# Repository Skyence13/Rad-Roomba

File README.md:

# Rad Roomba prototype design package

**System design revision 0.3 · 25 November 2026**  
An engineering baseline for a one-person-portable ROS 2 robot that surveys semitrailer and seacan floors at uranium facilities. The removable four-segment scintillation head is an independent hardware and firmware project. A dummy head lets the mobile platform proceed in parallel.

## Start here

1. Read **docs/Rad_Roomba_Design.pdf** for the full design, operating concept, decisions and gated development plan. Use **docs/Rad_Roomba_Design.docx** to revise it. The source register is in **docs/Sources.csv** and citations are clickable in both documents.
2. View **cad/renders/Rad_Roomba_Rev_D_Assembly.png** for the assembled robot and **cad/renders/Rad_Roomba_Rev_D_Detector_Head.png** for the detector detail. Open **cad/Mechanical_layout_D.pdf** for the three proposed mechanical views. Open **cad/Rad_Roomba_D.step** for the entire assembly or **cad/Detector_Head_D.step** for the removable head. Native source, dimensions, rebuild and geometry checks are in **cad/**.
3. Use **planning/requirements.csv** and **planning/verification.csv** together. Filter by owner and gate, attach evidence to a test, and update the linked requirement. **planning/risks.csv** and **planning/decisions.csv** track unresolved hazards and choices. Gate assignments run from G0 site inputs to G4 controlled pilot.
4. Use **planning/Detector_Head_RFQ.md** to request one full-size optical pair and comparable pricing for four. Use **planning/detector_bench_runs.csv** to capture test results; the RFQ explains its fields. Use **planning/Rad_Roomba_Current_BOM.xlsx** or **planning/prototype_bom.csv** for the current parts. Use **planning/Survey_Field_Checklist.md** for commissioning, shared-space scanning and guided follow-up, the separate secured unattended option, and charge service.
5. Read **interface/head_icd.md** before integrating the head. The samples under **examples/** show the wire and frame formats, geometry and site settings. **software/** contains a separate end-to-end mapping example for already-decoded data and the resulting map. Its input CSV is a simulation fixture. Read **software/Operator_Interface.md** for the operator workflow and open **software/guide_demo.html** in a browser to try the offline review queue.

## Project files

| Path | Use |
|---|---|
| docs/ | Full design in Word and PDF. Primary sources are indexed by ID in Sources.csv. |
| cad/ | Rev D editable assembly source, neutral STEP models, three-sheet PDF, dimensions and geometry checks. Coordinate units in the models are millimetres. |
| interface/ | Proposed modular head mechanical, power, independent bumper and isolated RS-485 contract. Includes the head descriptor, discovery, acquisition schema, CRC codec, host validation and tests. |
| examples/ | Normal and degraded frame, decoded transactions, a CRC-framed response, a head descriptor and bench registry, a concept geometry manifest and disabled site-profile examples. Units are explicit in files and in the ICD. |
| software/ | Python offline map demonstration, raw synthetic counts, poses, calculated cell estimates, valid exposure and a portable SVG. Also includes the operator web specification and an offline guided-tour demo with personnel present. |
| planning/ | Procurement crosswalk, OEM RFQ, operator checklist, detector run sheet, requirements, verification, risks and decisions. CSV files open in a spreadsheet editor. |
| reference/ | Original hardware workbook, user-supplied concept sketches, first concept and the preceding Revision B models. The current models are in cad/. Superseded Rev C models are in cad/previous_C/. |
| SHA256SUMS.txt | SHA-256 digest of each distributed file, excluding the checksum list itself. |

## Reproduce the included checks

From the unpacked **Rad_Roomba_Design_Package** directory:

```sh
python3 software/map_demo.py --self-test
python3 software/map_demo.py --out local_demo
```

The map example uses the Python standard library. The head interface tests additionally require the Python package **jsonschema** supporting Draft 2020-12. In an environment with it installed, run:

```sh
python3 interface/test_interface.py
```

For CAD, follow **cad/README.md**. The neutral STEP models and mechanical PDF are usable without rebuilding the CadQuery sources. On systems with GNU coreutils, check extracted file integrity from this directory with `sha256sum -c SHA256SUMS.txt`.

## Changes in revision 0.3

**Technicians in the trailer.** The intended shared-space mode permits technicians to stay in the trailer through a scan and while the robot moves between flagged areas. A person can stand alongside or behind the robot where there is sufficient clearance for the requested move. Determine the protected region from the body and projecting head throughout that move, detection latency, measured braking on the actual floor and a person's possible approach. A blocked route holds. For a hands-on check, inhibit traction, perform the check and step clear of the local motion envelope before deliberately restoring permission. The design also retains a separate secured, unattended option. Shared-space operation requires demonstration of personnel protection on the assembled robot. See the operator workflow and verification register.

**Head identity and acquisition.** Each attachment establishes the head type, serial, boot and descriptor once during discovery and binding. Subsequent count traffic carries interval measurements, timing, sequence and health. The host saves an attachment record and links every stored count to that record. Disconnection, reset, or loss of confidence in continuity requires re-establishing the binding. Recoverable packet loss on an intact connection uses the existing binding. The example transactions and tests in interface/ and examples/ show the distinction.

**CAD views.** The two standalone studio views in cad/renders/ come from the existing mechanical Rev D assembly and head. They share the same nominal dimensions as the engineering drawings.

## Changes introduced in revision 0.2

| Design review topic | Current location | Requirement |
|---|---|---|
| Shared web interface, gloved local controls, deliberate command authority | Design §2 and §7, software/Operator_Interface.md | RQ-041, RQ-042 |
| Qualified unattended scans, protective access controls and guided hotspot visits | Design §2, §4 and §7, offline guide_demo.html, operator field checklist | RQ-010, RQ-039, RQ-040, RQ-043 |
| Swappable packs, charge inlet, limited settings/data service | Design §4 and §8, current BOM workbook and rows R01–R06 | RQ-044, RQ-045 |
| Head-mounted MCU, identity, geometry and laboratory patch harness | Design §5–6, interface/head_icd.md, examples/head_descriptor.json | RQ-046, RQ-049 |
| 10 mm entrance gap, 3 or 5 mm rail projection and cantilever dynamics | Design §4–5, cad/Mechanical_layout_D.pdf, planning/detector_bench_runs.csv | RQ-047, RQ-048 |
| Pose at acquisition and saved locations for hand surveys | Design §1, §2 and §7, operator field checklist | RQ-050 |

The offline guide uses synthetic flags and no hardware connection. The proposed production web service, motion system and protective interlocks require implementation and field qualification.

## Baseline and use

The original workbook provides the 12.8 V / 8 Ah trial pack, warm-start power worksheet and prototype parts. The current procurement workbook adds the detector MCU, connector and bench kit, removable battery and charging hardware. Its sizing sheet models average consumption separately from peak supply allocation. The Rev B survey bar is a narrow placeholder. Rev C lengthened the head for four 80 × 100 mm apertures and separate upper references. Rev D retains that footprint, sets the entrance 10 mm above a level floor, and models a 7 mm clearance under the compliant contact rails. A 12 kg all-up packaging allowance and a one-hour energy scenario are trial assumptions. Weigh and qualify the real system for the actual site workflow.

The ore profile carries the stated 0.30 Bq/cm² investigation level and 0.40 Bq/cm² comparison criterion. A moving detection limit below 0.20 Bq/cm² is a proposed qualification target for a yet-to-be-specified minimum patch and field. The yellowcake profile awaits the radiation protection team's procedure and calibration. Raw counts and source, timing, location, coverage and sensitivity evidence remain essential to interpreting a reported Bq/cm² value.

All planning-register tests begin open. The software fixtures and CAD checks can be reproduced now. The build still requires component qualification, physical stopping and cold tests, radiometric calibration, independent field comparison and site authorization. Follow the evidence gates before treating the robot as an operational survey instrument.

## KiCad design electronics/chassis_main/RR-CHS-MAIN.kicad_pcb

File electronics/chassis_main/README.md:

# RR-CHS-MAIN rev A — chassis main board (stage 2, KiCad 9)

| | |
|---|---|
| Netlist source | `design/circuit.py` (stage 1, reviewed baseline, **not edited**) + `overrides.py` (stage-2 deviations S2-xx, stage-3 review fixes S3-xx and stage-4 follow-up fixes S4-xx, applied and checked on every build) |
| Board definition | `board.py` (libraries, import, notes) · `placement.py` (floor plan, net classes, planes, keep-outs, routing settings) · `placement_auto.py` (frozen auto-arranged passives, generated by `tools/freeze_auto.py`) |
| Board | 160 × 100 mm, **6 layers** (F sig / In1 GND / In2 sig / In3 sig / In4 power splits / B sig), 1.6 mm; 881 parts (768 − 1 removed + 3 stage-2 + 111 stage-3/4/5), 484 nets, 19 A3 schematic sheets |
| Status | see `STATUS.md`; routing result in section "Routing" below |

## Commands

```
python3 electronics/chassis_main/design/circuit.py          # stage-1 self-check (baseline)
python3 electronics/chassis_main/overrides.py               # stage-2 change log + self-check on the overridden netlist
python3 tools/eda/rrkicad.py sch   electronics/chassis_main/board.py              # schematic, netlist cross-check, ERC, PDF (~10 s)
python3 tools/eda/rrkicad.py build electronics/chassis_main/board.py --no-route   # + placed PCB, fan-out, escape, DRC, outputs (~2 min)
RR_FREEROUTING_JAVA_OPTS=-Xmx6g python3 tools/eda/rrkicad.py build electronics/chassis_main/board.py   # + autorouter (route/ SES cached)
tools/docker/kicad.sh python3 electronics/chassis_main/tools/fitcheck.py         # courtyard area per side, zone checks -> reports/fitcheck.json
python3 electronics/chassis_main/tools/cable_lengths.py                          # board-side list of the harness generator's lengths -> reports/cable_lengths.json
python3 electronics/chassis_main/tools/near_report.py 10                         # passives farther than 10 mm from their anchor pin
python3 electronics/chassis_main/tools/freeze_auto.py                            # freeze auto-arranged parts after a build
```
Delete `placement_auto.py` to let the auto-arranger re-place the passives (then freeze again).

## Frame mapping

`mechanical/common/board_envelopes.yaml` RR-CHS-MAIN (u, v) → tool board frame **(X, Y) = (u, v)**, no rotation, no offset:
origin = rear-left corner seen from above, X = u towards the robot's right (base_link −y), Y = v forward (base_link +x), top side up.
base_link = (−67 + Y, 80 − X, 83 + z) mm (board top at z = 84.6). Holes H1..H6 at the envelope (u, v); IMU U42 centred at (80, 67);
THERMAL_TO_BRIDGE pad u 50–110, v 30–70; front corners u < 14 / u > 146, v > 88. The pick-and-place file, `out/pinmap.json`, the STEP
models and the drill origin all use this frame.

## What is tool-checked (and what is not)

| Check | Result (last `--no-route` build, stage 5, 2026-11-28) |
|---|---|
| ERC | 0 errors, 0 warnings |
| Netlist cross-check: generated schematic → KiCad netlist vs definition, pin by pin | OK, 881 components (definition = circuit.py + overrides S2-S5) |
| DRC (placement, incl. the stage-3/4 custom chain rules: 7 rules in `RR-CHS-MAIN.kicad_dru`) | **0 errors**; 230 warnings (silk overlap 86, silk over copper 73, silk edge 9, dangling escape vias 61, copper sliver 1); schematic parity 0; courtyard overlaps 0; **1252 unconnected = board not routed** |
| Envelope | `tools/fitcheck.py`: no part outside the outline, no bottom part in the gap-pad area |
| Utilisation (courtyard area / 16 000 mm²) | top 59.5 %, bottom 21.9 % |

Not tool-checked: 1.0 mm between adjacent chain nodes (see "Clearances"), current capacity of the routed copper,
impedance of the USB / RS-485 pairs, thermal performance, real component heights (3D models are bounding-box envelopes).

## Placement

* Explicit (`placement.PLACE`, 148 parts): every connector (edge headers aligned to the edge from their real courtyards), relays,
  inductors, electrolytics, FETs, shunts, TVS, every IC, and the parts the guidance wants at the pins (bridge charge-pump / VM
  capacitors, crystal network, U10 boot/VCC). Floor plan as `layout_guidance.md` §2: power entry / charger / latch at the right rear,
  bridges, VMOT eFuse, 5 V buck and clamp on the gap pad, MCU + logic left, head branch front-left, RS-485 front-right.
* Passives (623): auto-arranged with `near=` the IC/connector pin they share a net with (`placement.auto_near`), on the side of that
  part (bottom for connector and through-hole anchors), then frozen. Quality (`reports/near_report.json`, test points excluded): of
  504 anchored passives 144 are ≤ 5 mm, 135 5–10 mm, 156 10–20 mm and **69 more than 20 mm** from their anchor pin (greedy auto-arranger
  on a dense board). Those are the first thing to improve by hand.
* Connector moves (IB-12 / IB-33): rear-right cluster = J_ESTOP, J_HANDS, J_COVER, **J_BUMP_R** (CLIK-Mate row) and J_NTC, **J_PAUSE**,
  **J_TOF3**, **J_TOF10**, **J_TOF6**, J_PAUX (GH rows); rear-left = J_MODE, J_BTN, J_BUMP_L, J_TOF9/8/2, J_PANEL, J_TOF5, USB, debug.
  Estimated ToF cables all ≤ 300 mm (`STAGE2_CHANGE_REQUESTS.md`).
* Outputs for the mechanical fit check: `reports/placement/RR-CHS-MAIN-unrouted.step`, `placement-top.png`, `placement-bottom.png`,
  `placement-assembly-top.pdf`, `placement-assembly-bottom.pdf`, `placement-copper-unrouted.pdf`, `RR-CHS-MAIN-pos.csv`.

## Copper

* In1.Cu: solid GND. In4.Cu splits (non-overlapping): 3V3 (logic, u 0.5–50, v 27–62), VMOT (u 58–102, v 37–62), VSYS (charger,
  u 104–159.5, v 42–60), VBAT_SW (rear band and right side, and the front-left head-branch area). rrkicad's plane fan-out ties SMD
  pads of those nets to their plane.
* Net classes: HC_PACK 1.0 mm, HC_VMOT / HC_BRANCH 0.8 mm, PWR_1A5 0.4 mm, SAFETY_CHAIN 0.4 mm / 0.2 mm clearance, signals 0.2 mm.
  These are the autorouter widths; the guidance widths for 20 A / 6.5 A / 5 A (12.3 / 2.6 / 1.8 mm) need pours or hand-drawn
  copper that is **not yet done** (open item).
* Keep-outs: 7 mm around every mounting hole (vias, parts), no vias under the IMU, no bottom parts on the gap pad.

## Clearances (stage 3, review M6: enforced by DRC)

* SAFETY_CHAIN net class (`placement.CHAIN_NETS`): 0.5 mm clearance to everything (the tool's plane fan-out now uses pairwise class
  clearance, `tools/eda/STATUS.md` defect 3).
* Custom DRC rules, written by `board.py` to `RR-CHS-MAIN.kicad_dru` from `placement.chain_rules()`; KiCad's DRC (kicad-cli, the tool's
  DRC step) loads the file from the project directory: **1.0 mm** from every high-side chain node (`CHAIN_HIGH`: CH_N0…CH_N9, CHAIN_END,
  K1_RUN, RUN_HD, RUN_12V, K1 coil / seal / set nodes, SET_CAP) to every supply net (`SUPPLY_NETS`: pack, VBAT_SW, VSYS, VMOT, V12_AUX,
  bridge outputs, branch outputs); **2.0 mm** loop-sense nets to heater nets (J_HEAD1 pins 4/5 are adjacent by contract and exempt as a
  pad pair); **10 mm** pad-to-pad between a chain test point and any other chain or supply test point (one bench clip cannot bypass an
  element; TP8/9/38/39/40/50/60/61/62 placed explicitly).
* In4 VBAT_SW / VMOT / VSYS splits: 1.0 mm zone clearance.
* Not covered by a rule: 1.0 mm between *adjacent* chain nodes (only the 0.5 mm class clearance), and the coil returns / clamp cathodes
  against GND (a GND short there is the low-side analogue of a bypass and cannot be kept away from the GND plane).

## Library resolution (the 15 parts without a footprint and the rejected symbol hints)

| Parts | Resolution | Geometry source |
|---|---|---|
| J_MODE, J_ESTOP, J_HANDS, J_COVER, J_DOCK, J_BUMP_L, J_BUMP_R, J_BTN | stock `Connector_Molex:Molex_CLIK-Mate_502443-xx70_1xNN-1MP_P2.00mm_Vertical` (MP solder tabs left without net) | KiCad library |
| U13, U16–U19 (TPS259470, RPW VQFN-HR-10 2 × 2) | `rr_local:TI_RPW0010A_VQFN-HR-10_2x2mm_PLACEHOLDER` | **from memory, PLACEHOLDER — redraw from the TI drawing** |
| U10 (LM61460, RJR VQFN-HR-14 4 × 3.5) | `rr_local:TI_RJR0014A_VQFN-HR-14_4x3.5mm_PLACEHOLDER` | **from memory, PLACEHOLDER** |
| W1 (DNP wire pads) | `rr_local:WirePads_2x2.5mm_P5.0mm` | stage-1 description |
| also: U8 TPS25982 (hint not a library name) | `rr_local:TI_TPS25982_VQFN-24_4x4mm_SplitPad_PLACEHOLDER` | generic QFN-24 perimeter, split pad **from memory** |
| L3, L4 (WE-LQS 5040) | `rr_local:L_Wuerth_WE-LQS-5040` | pads estimated from the 5 × 5 body, **verify** |
| L2 (XAL6060) | stock `L_Coilcraft_XAL6030-XXX` (same 6.36 × 6.56 base) | KiCad library, family assumption **verify** |
| Q4, Q5, Q40 (CSD18543Q3A) | `rr_local:VSON-8_3.3x3.3mm_P0.65mm_NexFET_G0.2` | stock NexFET land with pads 1–4 0.45 mm tall (stock 0.5 mm leaves 0.14 mm < fab 0.15 mm) |
| U42 (BMI088) | `rr_local:Bosch_LGA-16_4.5x3mm_P0.5mm_ClockwisePinNumbering` + local symbol `BMI088_SPI` (SDO tri-state) | pads copied from the stock Bosch footprint without its internal keep-out (the fan-out ignored it) |
| U5, U6 (DRV8874) | stock HTSSOP-16 EP variant without thermal vias (stage-1 hint has 0.2 mm drills) | KiCad library |
| U15, L60, SW1/2, TPs | stock `Texas_RGV0016A_VQFN-16…`, `L_CommonModeChoke_Coilank_ACM2012` (pin pairing **verify**), `SW_Tactile_SPST_NO_Straight_CK_PTS636Sx25SMTRLFS`, `TestPoint_Keystone_5019_Miniature` (hint misspelt) | KiCad library |
| Symbols | SOT-23 FETs → `Transistor_FET:BSS138/BSS84`, power FETs → `CSD18540Q5B/CSD18543Q3A`, U45 → `TCA9534`, K2/K3 → `Relay:G2RL-2` (renumbered S2-06b), J_HTR/J_LIDAR → `Conn_01x02`, shunts → `Device:R` | 12 generated box symbols remain (all-passive pins): LM74502, LTC4162-F, LM61460, LMR51610, TPS259470, INA3221, TPS2553, TPS3430, TPS25982, DRV8874, SM712, AOD4185 |

## Deviations from stage 1

`STAGE2_CHANGE_REQUESTS.md` (full list with reasons). Netlist/BOM: S2-01 J_PAUSE split from J_BTN (+R_PAUSE, D_PAUSE, D29 channels),
S2-02 J_HEAD1 → Mini-Fit Jr 2x5 (AWG 18), S2-04 R46 845 Ω (HEAD_HTR 3.96 A), S2-05 U42 pin 2 GND. Renumbering S2-06, library S2-07.
Decisions without netlist change: J_CM5 stays Micro-Fit with AWG 20 harness (IB-32 numbers), IB-28 contract proposals, IB-37 accept
offset. Placement: 6 layers, connector moves (IB-12/33).

**Stage 3 (review fixes, `docs/reviews/REVIEW_traction_inhibit.md`), S3-xx:** on-board edge-triggered two-contact REARM set stage
(U_SET, the K1 coil node no longer leaves the board), second diverse hold element U_HOLD in series with K1 pole B, D_RUN and the
low-side relay-return element U_LS (a RUN_12V short no longer energises the brake relays), K1 NC and K1_RUN readbacks, D_RSET (no
C_SET back-feed) and an active C_SET discharge, a second diverse head-loop channel (U46 + U21B in series), 47 kΩ isolation of every
expander pin on a chain-control node, U9 on its own tap, stiffer PB12/PD2 taps, IOX_D (U47, TCA9534 0x22), K2/K3 clamp Zeners 20 V,
chain clearance rules and test-point spacing. **Stage 4 (follow-up review `docs/reviews/REVIEW_traction_inhibit_followup.md`), S4-xx:** SET_READY comparator (U33B) and third stack FET Q_SETC (an early REARM press no longer empties the reservoir; readiness readable), R_SET 15 k, set qualification C_SF 2.2 µF (≥ 3.2 ms press), REARM set contact on IOX_A GPB6 at 1 kHz, CH_N6A tap and loop self-test FETs on IOX_D, D_RUN silicon + RUN_HD bleed, channel-B threshold 1.89 kΩ, own discharge-gate divider, D29 replaced by a 15 V D_AUX, net class CHAIN_CTRL and extended DRC rules (logic supplies, LED/gate nodes). Firmware list G1-G12 in `STAGE2_CHANGE_REQUESTS.md` section "Stage 4". **Stage 5 (`docs/reviews/REVIEW_traction_inhibit_stage4.md`), S5-xx:** top-side service pads SVC1-SVC10 (TP63-TP72, centre (133.0, 79.5)) with 220 k protection resistors R_SV2-R_SV10 for the latent-fault service tests (no test needs the board out), GPB6 readback 10 k/47 k + clamp, analog loop copy from LOOP_SNS, RT1 moved next to K1; firmware list H1-H7, body/harness notes §5.3. Full list, firmware change list (F1-F18) and harness/mechanical consequences:
`STAGE2_CHANGE_REQUESTS.md` section "Stage 3". Analysis: `electronics/analysis/chassis_safety_chain.md`.

## UNVERIFIED / open items

* PLACEHOLDER land patterns: U8, U10, U13, U16–U19 (redraw from TI drawings before fabrication); L3/L4 pads estimated; L2 family land.
* L60 common-mode choke winding pairing (1-2/4-3 vs 1-4/2-3) — a wrong pairing shorts RS-485 A to B through a winding.
* All stage-1 `verify=True` parts (132, BOM notes) plus the parts marked by stage 2 (`reports/summary.json` → `bom.verify`), notably
  LTC4162-F pin table, G2RL-2 / G6S-2 contact numbering, BMI088 pin numbers, TCA953x / MCP23S17 / FT230X pin numbers, Mini-Fit Jr MPNs.
* High-current copper (pours/pre-routes for HC_PACK 20 A, VMOT 6.5 A, heaters, V5_CM5 5 A), Kelvin routing for the shunts, USB/RS-485
  pair pre-routes, safety-chain grouping on L1: not done in this pass.
* 69 passives > 20 mm from their anchor pin (`reports/near_report.json`).
* Look sensors resolved (DEC-043): J_TOF4 = LOOK_FL, J_TOF5 = LOOK_RL, J_TOF6 = LOOK_RR, J_TOF7 = LOOK_FR (descriptions S3-N1).
* Stage-3 parts were placed by the auto-arranger and then frozen (`placement_auto.py`); U_SET/U_HOLD/U_LS/U21B/U46/U47 and their passives are not where a designer would put them (e.g. U21B and U46 apart, U_SET/U_HOLD 25 mm from K1): hand placement is the next step, before routing.
* Stage-3 UNVERIFIED: TLV3201 DBV pinout, TCA9534 pin table, B160 rating, TLP241A data, G6S-2 must-operate/release, TCA953x/STM32 input thresholds and pull-down values (STAGE2_CHANGE_REQUESTS.md 3.4). TPS3430 is now verified [D].
* Silkscreen: connector function legends, safety yellow box and "NOT A SAFETY-RATED CIRCUIT" text not yet added (references only).

## Routing (attempt of 2026-11-27, tool as it stood then)

> **Superseded by stage 3.** The stage-3 netlist (S3-xx) invalidates this routing: `RR-CHS-MAIN.kicad_pcb` is now the `--no-route` build of the stage-3 definition (**not routed**); the SES cached in `route/` belongs to the stage-2 netlist and must not be re-imported. The record below is kept for the routing engineer.

Run: `RR_FREEROUTING_JAVA_OPTS=-Xmx6g python3 tools/eda/rrkicad.py build electronics/chassis_main/board.py` with
`placement.routing()`: one Freerouting run, 780 s cap, no continue runs, rrkicad fine-pitch escape (default on for 6 layers;
`tools/eda/STATUS.md` reports it implemented and passing on STRESS-150, the README not yet updated) and the finisher.

| | |
|---|---|
| Plane fan-out / escape | 537 fan-out vias on GND, 3V3, VBAT_SW, VMOT, VSYS (154 pads left to the router); escape 82 vias + 2 direct pre-routes on U20M, U3, U42, U61, U8 (64 pads skipped, `reports/routing/summary-routed.json` → `routing.escape`) |
| Freerouting | 1169 unrouted items at start; **pass 1 took 769 s** (host load average 11-19 on 4 cores, other agents' builds), stopped by the 780 s cap after that pass with **802 unrouted** (score 403) |
| Result in KiCad (`RR-CHS-MAIN.kicad_pcb`) | 2486 tracks, 970 vias; **802 open connections** (KiCad ratsnest; DRC lists the first 499: `reports/open_connections.txt` with nets and coordinates); DRC **1 error** (shorting_items: an RS_RO via through the NT1 net-tie copper polygon, see tool defects), 145 warnings (silk 119, 25 dangling escape vias, 1 dangling track); schematic parity 0; ERC 0/0 |
| Status | **FAIL** — partially routed. Planes, fan-out, escape pre-routes intact; the SES is cached in `route/` |
| Time | build 00:48 → Freerouting end 01:03 (820 s routing) + post stage 38 s |
| Open connections by net (first 499 listed) | V5_AUX 27, 3V3 14, VREF_3V0 13, V5_BUCK 10, VBAT_RAW 8, VBAT_SW 8, CHG_VIN 8, COIL_RTN 8, PSW_SRC 7, RUN_12V 7, HW_LATCH_RB 7, VSYS 6, … (power nets dominate: their pads were left to the router where no fan-out via fit) |

How the post stage was run: the build's own `_post` crashed in the tool's new unused-escape clean-up
(`pcb.py _remove_unused_escapes`: `TypeError: 'SwigPyObject' object is not iterable`; pcb.py was being edited during the run) and
the host then started the finisher on an un-imported board (1165 "open"), which was stopped. The SES was imported with
`tools/docker/kicad.sh python3 tools/eda/rrkicad.py _post electronics/chassis_main/board.py` after moving
`route/escape_vias.json` aside (that file only drives the clean-up), so unused escape vias remain (25 via_dangling warnings).
A plain `build` re-uses the cached SES but will hit the same crash until the tool is fixed.

Judgement — what it takes to finish: the router is CPU-starved and far from done after one pass (31 % of the items routed in
13 min); STRESS-150 needed ~20-40 passes. Realistic routes to completion, in order of effect: (1) hand-drawn copper for the power
nets that dominate the open list (pours/pre-routes for VBAT_RAW/PSW_SRC/VBAT_SW at the power entry, VMOT, VSYS, V5_BUCK/V5_CM5,
heater branches) and extend the In4 splits / add In3 pours for V5_AUX and VREF_3V0; (2) fix the ~70 passives placed > 20 mm from
their pins and the dense rear-left corner; (3) then several continue runs of 20-30 min each on an otherwise idle machine plus the
finisher once the tool's import is fixed; (4) whatever remains (expect tens of connections) by hand in KiCad. The safety-chain group
routing and the critical-net pre-routes of guidance §6 are not done and should precede (3).

Next fixes in the definition (not applied, to keep the routed files consistent with `board.py`): copper + via keep-out over NT1
(Freerouting does not see net-tie polygons), the 6 pin-to-pin "violations" Freerouting reports on U1 (SOT-23-8 0.15 mm gaps + 25 um
DSN margin) are harmless.

## Tool defects found (tools/eda not edited; worked around in the board definition)
1. Plane fan-out places vias with the via net's class clearance, not the neighbour's → SAFETY_CHAIN DRC clearance lowered to 0.2 mm.
2. Plane fan-out ignores footprint-internal rule areas (Bosch LGA keep-out) and net-tie copper polygons → local IMU footprint without
   rule area + board via keep-out; NT1 moved and `zone_connect="none"`; Freerouting likewise routed a via through NT1's polygon.
3. A footprint-only rule area on B.Cu (no tracks/vias/copper ban) is exported to the DSN as a full B.Cu keep-out → removed once the
   placement was frozen.
4. KiCad's DRC report lists at most 499 unconnected items, so `summary.json` → `unconnected` saturates at 499 (true count 802 here
   after routing); the summary should use the connectivity count.
5. Post stage crash in `_remove_unused_escapes` (above) and the host then running the finisher on an un-routed board.
6. Auto-arrange is weak on dense two-sided boards (69 passives > 20 mm from their anchor pin); with escape keep-aways it can fail
   ("no room") when passives are asked to stay on the IC's side.

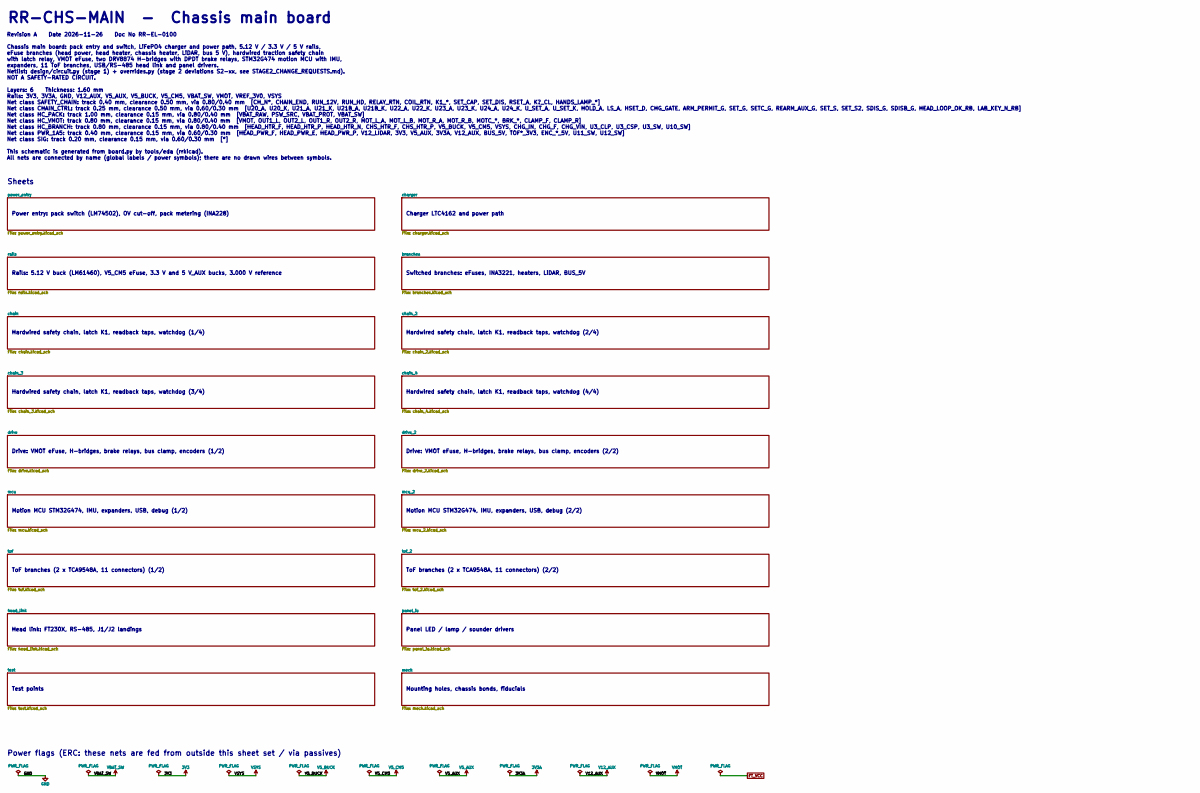
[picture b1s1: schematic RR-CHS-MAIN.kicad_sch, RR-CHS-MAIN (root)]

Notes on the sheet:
RR-CHS-MAIN - Chassis main board
Revision A Date 2026-11-26 Doc No RR-EL-0100 Chassis main board: pack entry and switch, LiFePO4 charger and power path, 5.12 V / 3.3 V / 5 V rails, eFuse branches (head power, head heater, chassis heater, LiDAR, bus 5 V), hardwired traction safety chain with latch relay, VMOT eFuse, two DRV8874 H-b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
Sheets
Power entry: pack switch (LM74502), OV cut-off, pack metering (INA228)
Charger LTC4162 and power path
Rails: 5.12 V buck (LM61460), V5_CM5 eFuse, 3.3 V and 5 V_AUX bucks, 3.000 V reference
Switched branches: eFuses, INA3221, heaters, LiDAR, BUS_5V
Hardwired safety chain, latch K1, readback taps, watchdog (1/4)
Hardwired safety chain, latch K1, readback taps, watchdog (2/4)
Hardwired safety chain, latch K1, readback taps, watchdog (3/4)
Hardwired safety chain, latch K1, readback taps, watchdog (4/4)
Drive: VMOT eFuse, H-bridges, brake relays, bus clamp, encoders (1/2)
Drive: VMOT eFuse, H-bridges, brake relays, bus clamp, encoders (2/2)
Motion MCU STM32G474, IMU, expanders, USB, debug (1/2)
Motion MCU STM32G474, IMU, expanders, USB, debug (2/2)
ToF branches (2 x TCA9548A, 11 connectors) (1/2)
ToF branches (2 x TCA9548A, 11 connectors) (2/2)
Head link: FT230X, RS-485, J1/J2 landings
Panel LED / lamp / sounder drivers
Test points
Mounting holes, chassis bonds, fiducials
Power flags (ERC: these nets are fed from outside this sheet set / via passives)

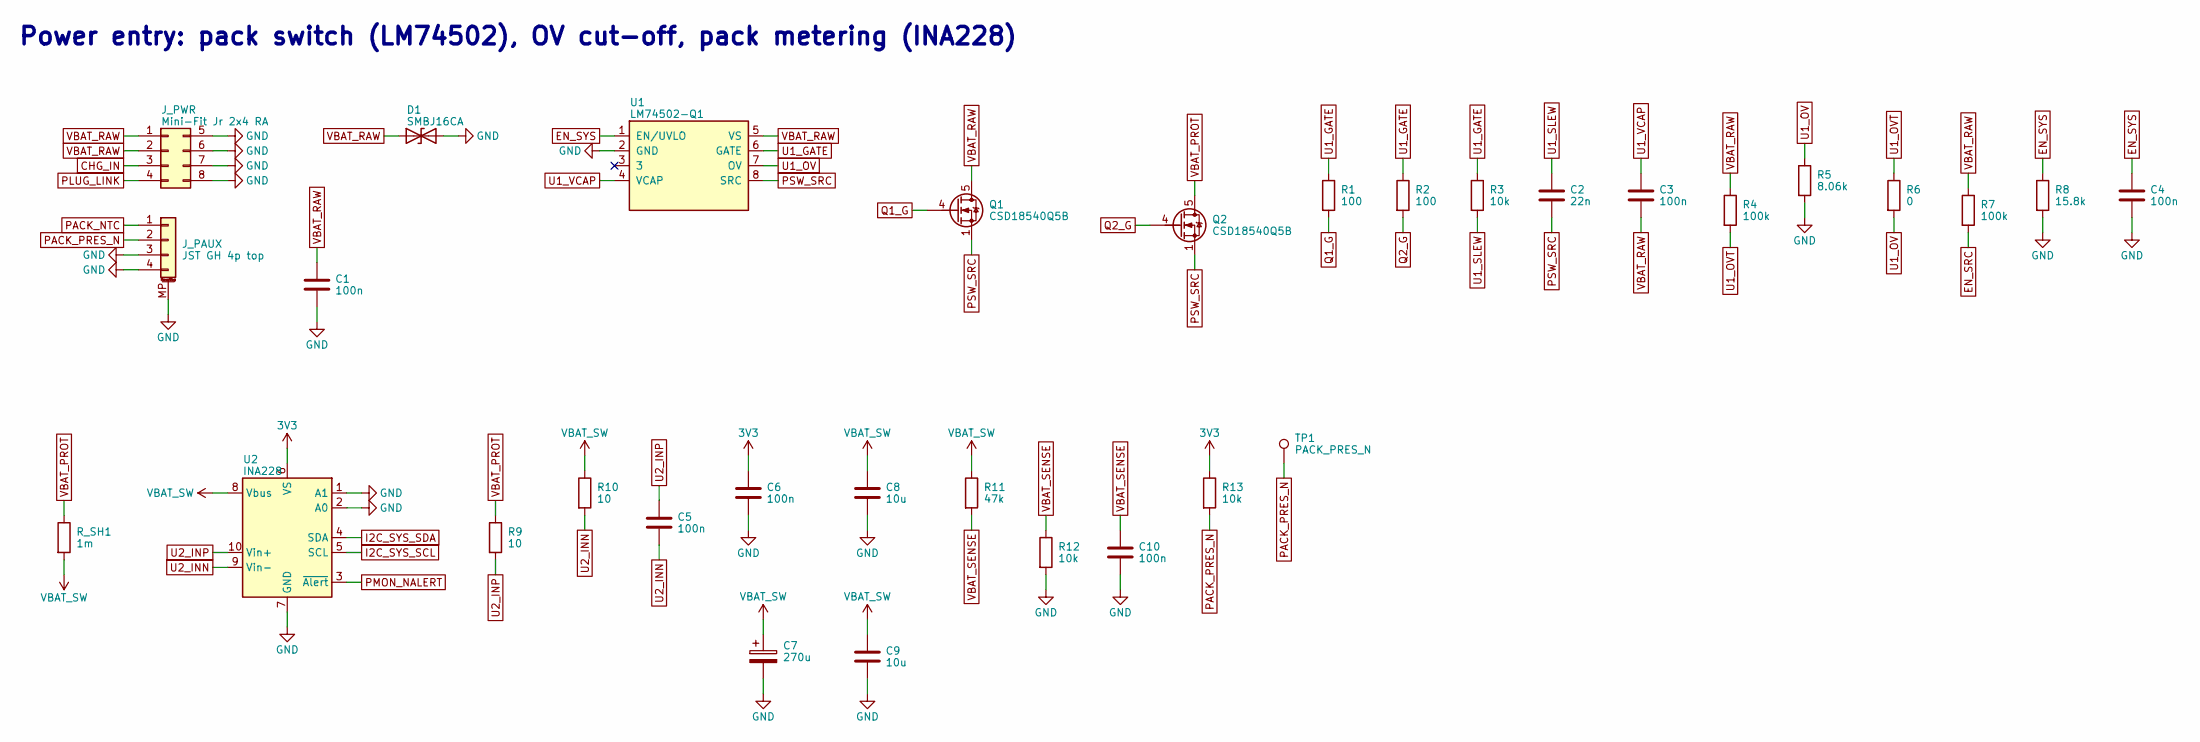
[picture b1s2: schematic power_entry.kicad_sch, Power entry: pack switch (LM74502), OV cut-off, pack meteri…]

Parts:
C1, C3, C4, C5, C6, C10: 100n; C_0603_1608Metric; MPN CC0603KRX7R9BB104
C2: 22n; C_0603_1608Metric; MPN CC0603KRX7R9BB223
C7: 270u; CP_Elec_10x10.5; MPN EEHZA1V271P
C8, C9: 10u; C_1206_3216Metric; MPN GRM31CR71E106KA12L
D1: SMBJ16CA; D_SMB; MPN SMBJ16CA
J_PAUX: JST GH 4p top; JST_GH_BM04B-GHS-TBT_1x04-1MP_P1.25mm_Vertical; MPN BM04B-GHS-TBT(LF)(SN)
J_PWR: Mini-Fit Jr 2x4 RA; Molex_Mini-Fit_Jr_5569-08A2_2x04_P4.20mm_Horizontal; MPN 39-30-1080
Q1, Q2: CSD18540Q5B; TDSON-8-1; MPN CSD18540Q5B
R1, R2: 100; R_0603_1608Metric; MPN RC0603FR-07100RL
R3, R12, R13: 10k; R_0603_1608Metric; MPN RC0603FR-0710KL
R4, R7: 100k; R_0603_1608Metric; MPN RC0603FR-07100KL
R5: 8.06k; R_0603_1608Metric; MPN RC0603FR-078K06L
R6: 0; R_0603_1608Metric; MPN RC0603FR-070RL
R8: 15.8k; R_0603_1608Metric; MPN RC0603FR-0715K8L
R9, R10: 10; R_0603_1608Metric; MPN RC0603FR-0710RL
R11: 47k; R_0603_1608Metric; MPN RC0603FR-0747KL
R_SH1: 1m; R_2512_6332Metric; MPN WSL25121L000FEA
TP1: PACK_PRES_N; TestPoint_Keystone_5019_Miniature; MPN 5019
U1: LM74502-Q1; SOT-23-8; MPN LM74502QDDFRQ1
U2: INA228; VSSOP-10_3x3mm_P0.5mm; MPN INA228AIDGSR

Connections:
3V3: C6.1, R13.1, U2.6 (VS); also elsewhere on the board
CHG_IN: J_PWR.3; also elsewhere on the board
EN_SRC: R7.2; also elsewhere on the board
EN_SYS: C4.1, R8.1, U1.1 (EN/UVLO); also elsewhere on the board
GND: C1.2, C4.2, C6.2, C7.2, C8.2, C9.2, C10.2, D1.2 (A2), J_PAUX.3, J_PAUX.4, J_PAUX.MP (MountPin), J_PWR.5, J_PWR.6, J_PWR.7, J_PWR.8, R5.2, R8.2, R12.2, U1.2 (GND), U2.1 (A1), U2.2 (A0), U2.7 (GND); also elsewhere on the board
I2C_SYS_SCL: U2.5 (SCL); also elsewhere on the board
I2C_SYS_SDA: U2.4 (SDA); also elsewhere on the board
PACK_NTC: J_PAUX.1; also elsewhere on the board
PACK_PRES_N: J_PAUX.2, R13.2, TP1.1; also elsewhere on the board
PLUG_LINK: J_PWR.4; also elsewhere on the board
PMON_NALERT: U2.3 (~Alert); also elsewhere on the board
PSW_SRC: C2.2, Q1.1 (S), Q1.2 (S), Q1.3 (S), Q2.1 (S), Q2.2 (S), Q2.3 (S), U1.8 (SRC)
Q1_G: Q1.4 (G), R1.2
Q2_G: Q2.4 (G), R2.2
U1_GATE: R1.1, R2.1, R3.1, U1.6 (GATE)
U1_OV: R5.1, R6.2, U1.7 (OV)
U1_OVT: R4.2, R6.1
U1_SLEW: C2.1, R3.2
U1_VCAP: C3.1, U1.4 (VCAP)
U2_INN: C5.2, R10.2, U2.9 (Vin-)
U2_INP: C5.1, R9.2, U2.10 (Vin+)
VBAT_PROT: Q2.5 (D), R9.1, R_SH1.1
VBAT_RAW: C1.1, C3.2, D1.1 (A1), J_PWR.1, J_PWR.2, Q1.5 (D), R4.1, R7.1, U1.5 (VS)
VBAT_SENSE: C10.1, R11.2, R12.1; also elsewhere on the board
VBAT_SW: C7.1, C8.1, C9.1, R10.1, R11.1, R_SH1.2, U2.8 (Vbus); also elsewhere on the board

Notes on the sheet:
Power entry: pack switch (LM74502), OV cut-off, pack metering (INA228)

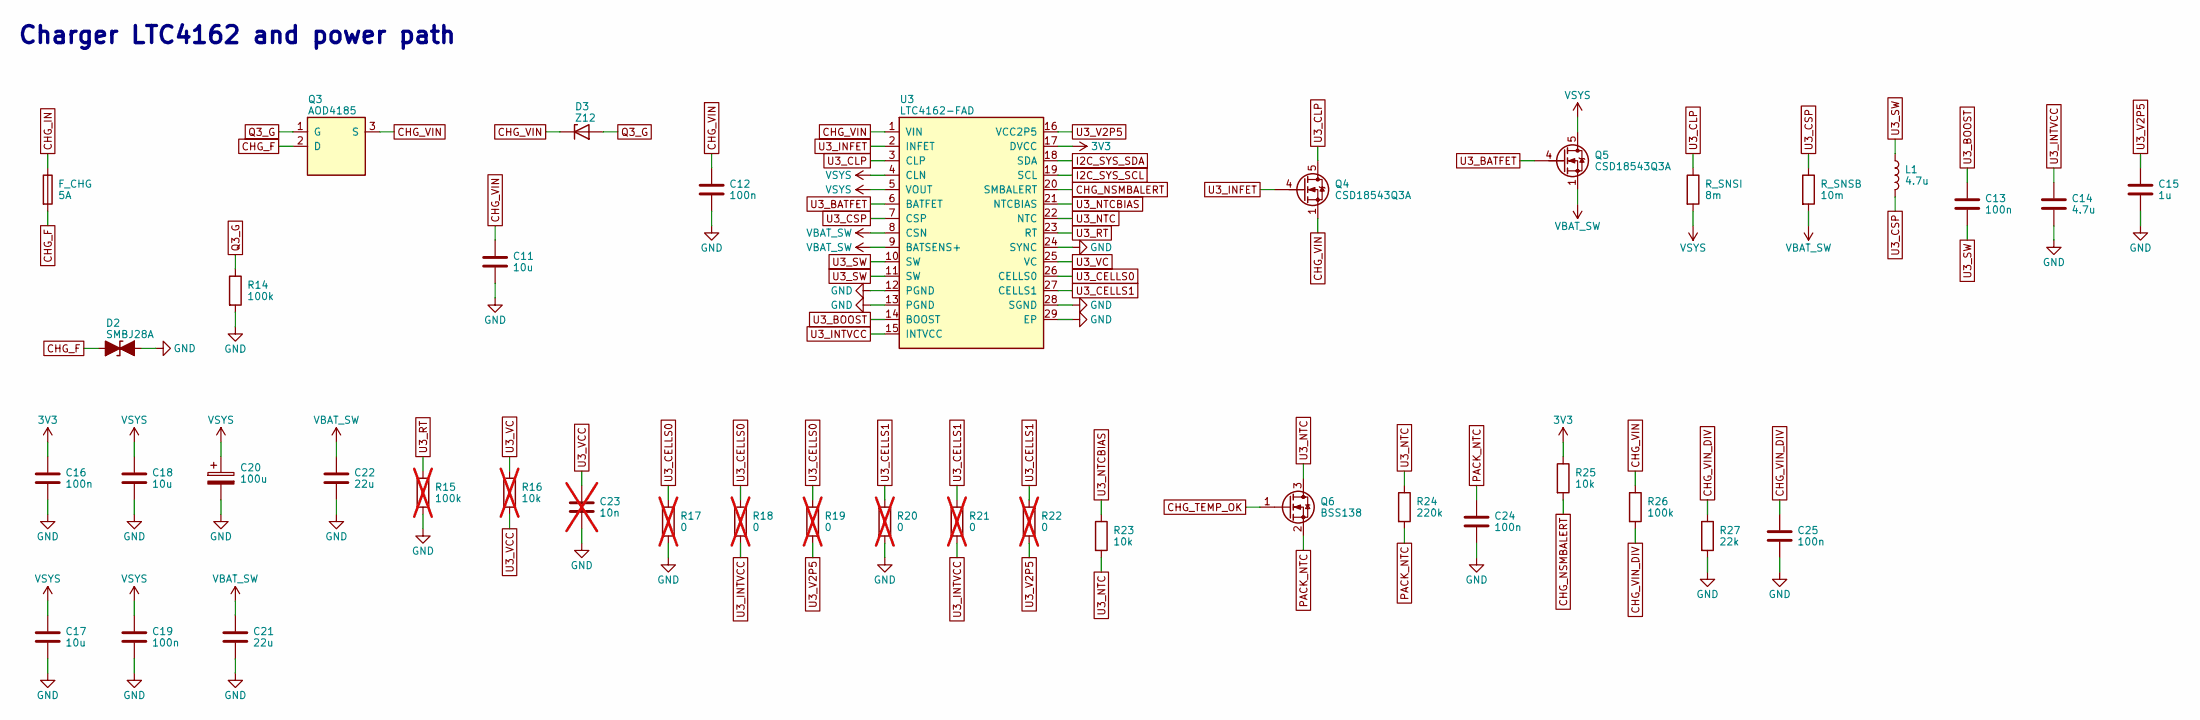
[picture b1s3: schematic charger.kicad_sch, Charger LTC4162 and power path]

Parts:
C11, C17, C18: 10u; C_1210_3225Metric; MPN GRM32ER71H106KA12L
C12, C13, C16, C19, C24, C25: 100n; C_0603_1608Metric; MPN CC0603KRX7R9BB104
C14: 4.7u; C_0805_2012Metric; MPN GRM21BR71C475KA73L
C15: 1u; C_0603_1608Metric; MPN GRM188R71C105KA12D
C20: 100u; CP_Elec_10x10.5; MPN EEHZA1H101P
C21, C22: 22u; C_1210_3225Metric; MPN GRM32ER71E226KE15L
C23: 10n; C_0603_1608Metric; MPN CC0603KRX7R9BB103; not fitted
D2: SMBJ28A; D_SMB; MPN SMBJ28A
D3: Z12; D_SOD-123; MPN BZT52C12-7-F
F_CHG: 5A; Fuse_Littelfuse-NANO2-451_453; MPN 0453005.MR
L1: 4.7u; L_Coilcraft_XAL5050-XXX; MPN XAL5050-472MEC
Q3: AOD4185; TO-252-2; MPN AOD4185
Q4, Q5: CSD18543Q3A; VSON-8_3.3x3.3mm_P0.65mm_NexFET_G0.2; MPN CSD18543Q3A
Q6: BSS138; SOT-23; MPN BSS138
R14, R26: 100k; R_0603_1608Metric; MPN RC0603FR-07100KL
R15: 100k; R_0603_1608Metric; MPN RC0603FR-07100KL; not fitted
R16: 10k; R_0603_1608Metric; MPN RC0603FR-0710KL; not fitted
R17, R18, R19, R20, R21, R22: 0; R_0603_1608Metric; MPN RC0603FR-070RL; not fitted
R23, R25: 10k; R_0603_1608Metric; MPN RC0603FR-0710KL
R24: 220k; R_0603_1608Metric; MPN RC0603FR-07220KL
R27: 22k; R_0603_1608Metric; MPN RC0603FR-0722KL
R_SNSB: 10m; R_1206_3216Metric; MPN WSL1206R0100FEA
R_SNSI: 8m; R_1206_3216Metric; MPN WSL12068L000FEA
U3: LTC4162-FAD; QFN-28-1EP_4x5mm_P0.5mm_EP2.65x3.65mm; MPN LTC4162EUFD-FAD#PBF

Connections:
3V3: C16.1, R25.1, U3.17 (DVCC); also elsewhere on the board
CHG_F: D2.1 (A1), F_CHG.2, Q3.2 (D)
CHG_IN: F_CHG.1; also elsewhere on the board
CHG_NSMBALERT: R25.2, U3.20 (SMBALERT); also elsewhere on the board
CHG_TEMP_OK: Q6.1 (G); also elsewhere on the board
CHG_VIN: C11.1, C12.1, D3.1 (K), Q3.3 (S), Q4.1 (S), Q4.2 (S), Q4.3 (S), R26.1, U3.1 (VIN)
CHG_VIN_DIV: C25.1, R26.2, R27.1; also elsewhere on the board
GND: C11.2, C12.2, C14.2, C15.2, C16.2, C17.2, C18.2, C19.2, C20.2, C21.2, C22.2, C23.2, C24.2, C25.2, D2.2 (A2), R14.2, R15.2, R17.2, R20.2, R27.2, U3.12 (PGND), U3.13 (PGND), U3.24 (SYNC), U3.28 (SGND), U3.29 (EP); also elsewhere on the board
I2C_SYS_SCL: U3.19 (SCL); also elsewhere on the board
I2C_SYS_SDA: U3.18 (SDA); also elsewhere on the board
PACK_NTC: C24.1, Q6.2 (S), R24.2; also elsewhere on the board
Q3_G: D3.2 (A), Q3.1 (G), R14.1
U3_BATFET: Q5.4 (G), U3.6 (BATFET)
U3_BOOST: C13.1, U3.14 (BOOST)
U3_CELLS0: R17.1, R18.1, R19.1, U3.26 (CELLS0)
U3_CELLS1: R20.1, R21.1, R22.1, U3.27 (CELLS1)
U3_CLP: Q4.5 (D), R_SNSI.1, U3.3 (CLP)
U3_CSP: L1.2, R_SNSB.1, U3.7 (CSP)
U3_INFET: Q4.4 (G), U3.2 (INFET)
U3_INTVCC: C14.1, R18.2, R21.2, U3.15 (INTVCC)
U3_NTC: Q6.3 (D), R23.2, R24.1, U3.22 (NTC); also elsewhere on the board
U3_NTCBIAS: R23.1, U3.21 (NTCBIAS)
U3_RT: R15.1, U3.23 (RT)
U3_SW: C13.2, L1.1, U3.10 (SW), U3.11 (SW)
U3_V2P5: C15.1, R19.2, R22.2, U3.16 (VCC2P5)
U3_VC: R16.1, U3.25 (VC)
U3_VCC: C23.1, R16.2
VBAT_SW: C21.1, C22.1, Q5.1 (S), Q5.2 (S), Q5.3 (S), R_SNSB.2, U3.8 (CSN), U3.9 (BATSENS+); also elsewhere on the board
VSYS: C17.1, C18.1, C19.1, C20.1, Q5.5 (D), R_SNSI.2, U3.4 (CLN), U3.5 (VOUT); also elsewhere on the board

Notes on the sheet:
Charger LTC4162 and power path

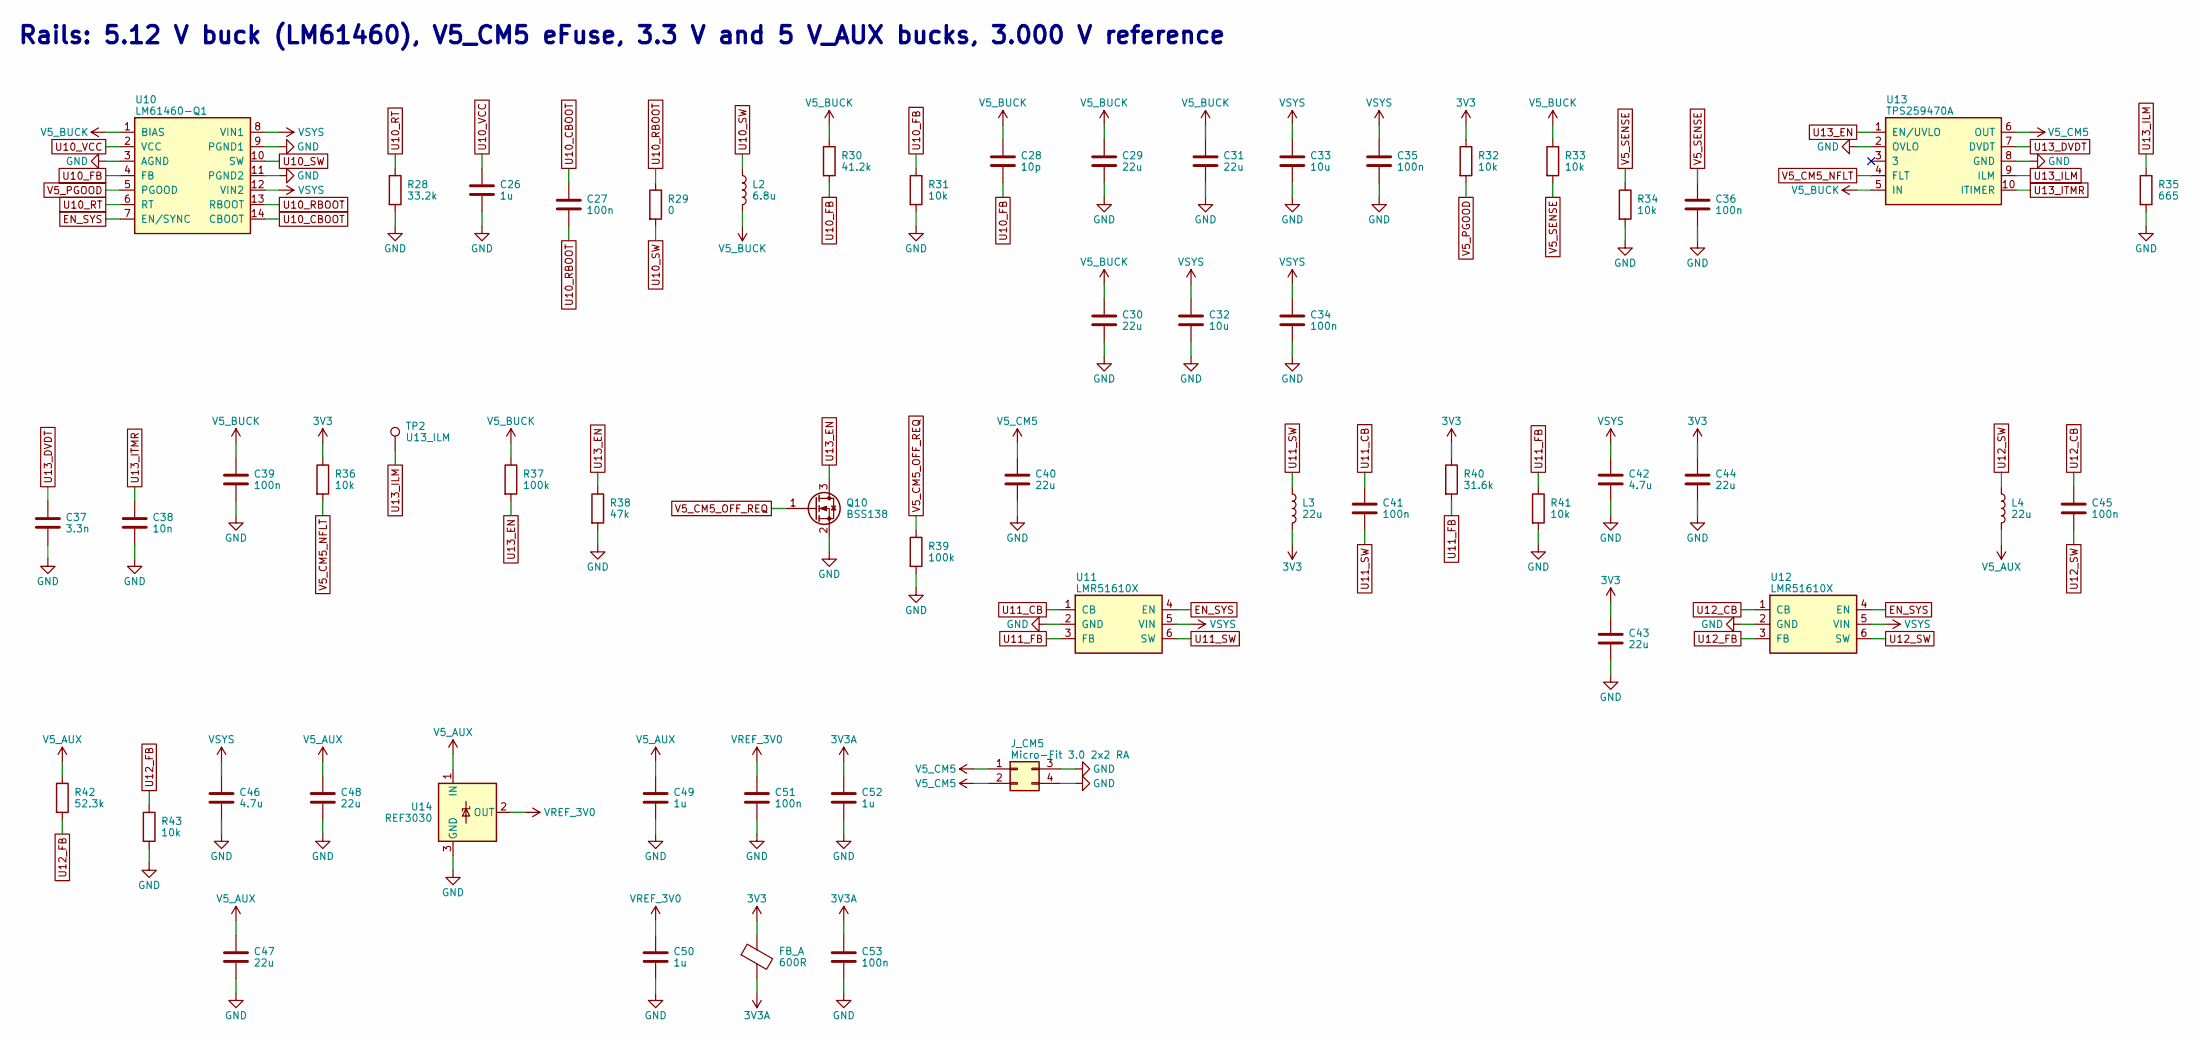
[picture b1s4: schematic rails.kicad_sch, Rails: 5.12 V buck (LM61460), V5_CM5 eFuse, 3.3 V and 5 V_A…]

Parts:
C26, C49, C50, C52: 1u; C_0603_1608Metric; MPN GRM188R71C105KA12D
C27, C34, C35, C36, C39, C41, C45, C51, C53: 100n; C_0603_1608Metric; MPN CC0603KRX7R9BB104
C28: 10p; C_0603_1608Metric; MPN CC0603JRNPO9BN100
C29, C30, C31, C40, C43, C44, C47, C48: 22u; C_1206_3216Metric; MPN GRM31CR71A226KE15L
C32, C33: 10u; C_1210_3225Metric; MPN GRM32ER71H106KA12L
C37: 3.3n; C_0603_1608Metric; MPN CC0603KRX7R9BB332
C38: 10n; C_0603_1608Metric; MPN CC0603KRX7R9BB103
C42, C46: 4.7u; C_1206_3216Metric; MPN GRM31CR71H475KA12L
FB_A: 600R; L_0603_1608Metric; MPN BLM18KG601SN1D
J_CM5: Micro-Fit 3.0 2x2 RA; Molex_Micro-Fit_3.0_43045-0400_2x02_P3.00mm_Horizontal; MPN 43045-0400
L2: 6.8u; L_Coilcraft_XAL6030-XXX; MPN XAL6060-682MEC
L3, L4: 22u; L_Wuerth_WE-LQS-5040; MPN 74404054220
Q10: BSS138; SOT-23; MPN BSS138
R28: 33.2k; R_0603_1608Metric; MPN RC0603FR-0733K2L
R29: 0; R_0603_1608Metric; MPN RC0603FR-070RL
R30: 41.2k; R_0603_1608Metric; MPN RC0603FR-0741K2L
R31, R32, R33, R34, R36, R41, R43: 10k; R_0603_1608Metric; MPN RC0603FR-0710KL
R35: 665; R_0603_1608Metric; MPN RC0603FR-07665RL
R37, R39: 100k; R_0603_1608Metric; MPN RC0603FR-07100KL
R38: 47k; R_0603_1608Metric; MPN RC0603FR-0747KL
R40: 31.6k; R_0603_1608Metric; MPN RC0603FR-0731K6L
R42: 52.3k; R_0603_1608Metric; MPN RC0603FR-0752K3L
TP2: U13_ILM; TestPoint_Keystone_5019_Miniature; MPN 5019
U10: LM61460-Q1; TI_RJR0014A_VQFN-HR-14_4x3.5mm_PLACEHOLDER; MPN LM61460AASQRJRRQ1
U11, U12: LMR51610X; SOT-23-6; MPN LMR51610XDBVR
U13: TPS259470A; TI_RPW0010A_VQFN-HR-10_2x2mm_PLACEHOLDER; MPN TPS259470ARPWR
U14: REF3030; SOT-23; MPN REF3030AIDBZR

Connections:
3V3: C43.1, C44.1, FB_A.1, L3.2, R32.1, R36.1, R40.1; also elsewhere on the board
3V3A: C52.1, C53.1, FB_A.2; also elsewhere on the board
EN_SYS: U10.7 (EN/SYNC), U11.4 (EN), U12.4 (EN); also elsewhere on the board
GND: C26.2, C29.2, C30.2, C31.2, C32.2, C33.2, C34.2, C35.2, C36.2, C37.2, C38.2, C39.2, C40.2, C42.2, C43.2, C44.2, C46.2, C47.2, C48.2, C49.2, C50.2, C51.2, C52.2, C53.2, J_CM5.3, J_CM5.4, Q10.2 (S), R28.2, R31.2, R34.2, R35.2, R38.2, R39.2, R41.2, R43.2, U10.3 (AGND), U10.9 (PGND1), U10.11 (PGND2), U11.2 (GND), U12.2 (GND), U13.2 (OVLO), U13.8 (GND), U14.3 (GND); also elsewhere on the board
U10_CBOOT: C27.1, U10.14 (CBOOT)
U10_FB: C28.2, R30.2, R31.1, U10.4 (FB)
U10_RBOOT: C27.2, R29.1, U10.13 (RBOOT)
U10_RT: R28.1, U10.6 (RT)
U10_SW: L2.1, R29.2, U10.10 (SW)
U10_VCC: C26.1, U10.2 (VCC)
U11_CB: C41.1, U11.1 (CB)
U11_FB: R40.2, R41.1, U11.3 (FB)
U11_SW: C41.2, L3.1, U11.6 (SW)
U12_CB: C45.1, U12.1 (CB)
U12_FB: R42.2, R43.1, U12.3 (FB)
U12_SW: C45.2, L4.1, U12.6 (SW)
U13_DVDT: C37.1, U13.7 (DVDT)
U13_EN: Q10.3 (D), R37.2, R38.1, U13.1 (EN/UVLO)
U13_ILM: R35.1, TP2.1, U13.9 (ILM)
U13_ITMR: C38.1, U13.10 (ITIMER)
V5_AUX: C47.1, C48.1, C49.1, L4.2, R42.1, U14.1 (IN); also elsewhere on the board
V5_BUCK: C28.1, C29.1, C30.1, C31.1, C39.1, L2.2, R30.1, R33.1, R37.1, U10.1 (BIAS), U13.5 (IN)
V5_CM5: C40.1, J_CM5.1, J_CM5.2, U13.6 (OUT); also elsewhere on the board
V5_CM5_NFLT: R36.2, U13.4 (FLT); also elsewhere on the board
V5_CM5_OFF_REQ: Q10.1 (G), R39.1; also elsewhere on the board
V5_PGOOD: R32.2, U10.5 (PGOOD); also elsewhere on the board
V5_SENSE: C36.1, R33.2, R34.1; also elsewhere on the board
VREF_3V0: C50.1, C51.1, U14.2 (OUT); also elsewhere on the board
VSYS: C32.1, C33.1, C34.1, C35.1, C42.1, C46.1, U10.8 (VIN1), U10.12 (VIN2), U11.5 (VIN), U12.5 (VIN); also elsewhere on the board

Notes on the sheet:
Rails: 5.12 V buck (LM61460), V5_CM5 eFuse, 3.3 V and 5 V_AUX bucks, 3.000 V reference
